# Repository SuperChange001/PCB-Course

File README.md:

# PCB Course

Materials for the PCB course

## Preparation
1. Please clone this repo to to your PC
2. Download and install Eagele with the version which matches your Operating System:
   - [Download Eagle](https://www.autodesk.com/products/eagle/free-download)
   - The first time you open the Eagle, it may ask you to log in, there you should use your university email address to register and log in.

## Folder structure

``` text
.
├── xmas tree
│   ├── tree_pcb.brd
│   ├── tree_pcb.sch
│   └── xmas_tree.lbr
├── esp32 shield
│   ├── design_template
│   ├── old_design
│   └── esp32_shield.lbr
├── utils
│   ├── jlcpcb_cam.cam
│   ├── jlc_pcb.dru
│   ├── voltera-cam.cam
│   └── voltera-dru.dru
└── README.md
```
1. `xmas tree` contains the material for the beginner course
2. `esp32 shield` contains the material for the advanced course
3. `utils` host files that are shared

## Acknowledgement
The christmas tree project is inspird by
* [Brian-Lough-Hardware](https://github.com/witnessmenow/Brian-Lough-Hardware/tree/main/Hardware/Side%20Mounted%20LED%20Tester)

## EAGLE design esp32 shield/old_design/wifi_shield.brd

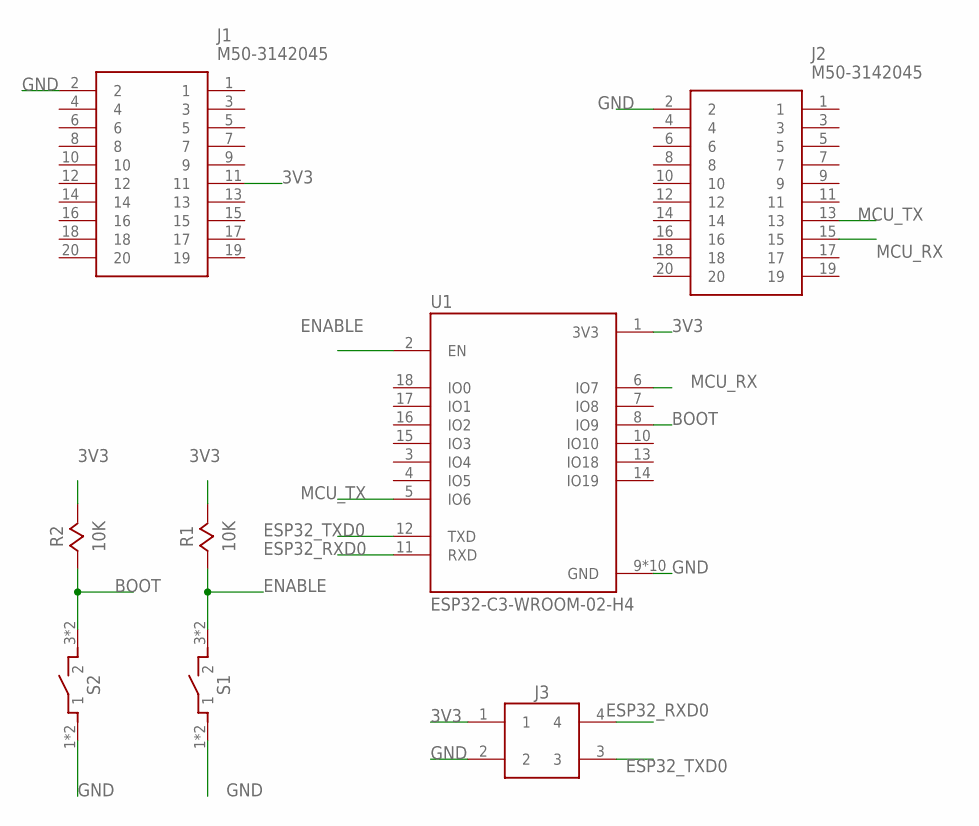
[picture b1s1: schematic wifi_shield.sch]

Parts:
J1, J2: M50-3142045; M503142045
J3: MALE_HEADER_4X1; 4X1_HEADER
R1, R2: 10K; 0805
S1, S2: TACTILE-SWITCH
U1: ESP32-C3-WROOM-02-H4; MODULE_ESP32-C3-WROOM-02-H4

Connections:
3V3: J1.11, J3.1, R1.2, R2.2, U1.1 (3V3)
BOOT: R2.1, S2.3 (2), S2.4 (2), U1.8 (IO9)
ENABLE: R1.1, S1.3 (2), S1.4 (2), U1.2 (EN)
ESP32_RXD0: J3.4, U1.11 (RXD)
ESP32_TXD0: J3.3, U1.12 (TXD)
GND: J1.2, J2.2, J3.2, S1.1, S1.2 (1), S2.1, S2.2 (1), U1.9 (GND), U1.19 (GND), U1.20 (GND), U1.21 (GND), U1.22 (GND), U1.23 (GND), U1.24 (GND), U1.25 (GND), U1.26 (GND), U1.27 (GND)
MCU_RX: J2.15, U1.6 (IO7)
MCU_TX: J2.13, U1.5 (IO6)

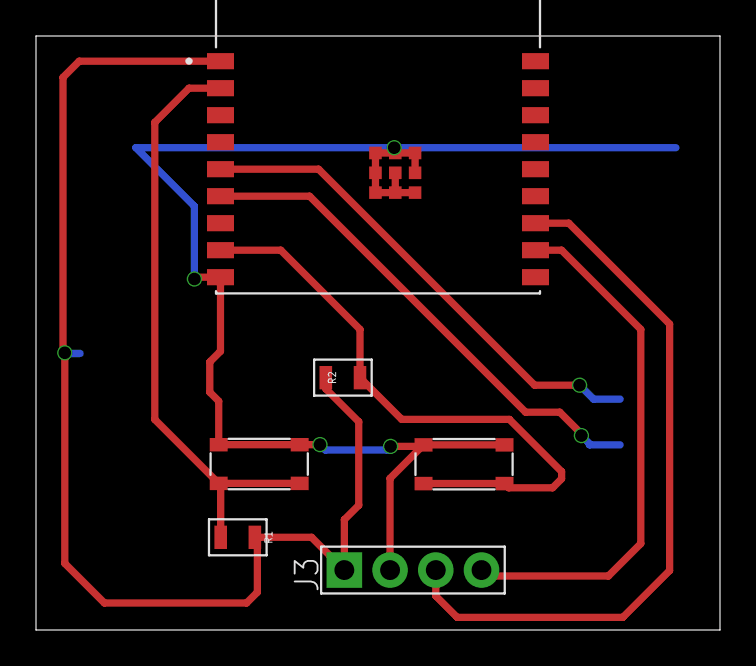
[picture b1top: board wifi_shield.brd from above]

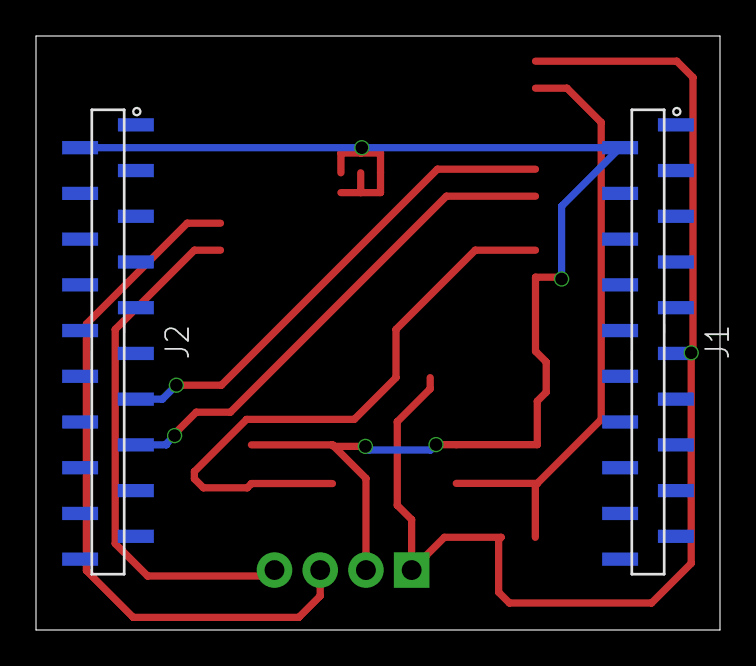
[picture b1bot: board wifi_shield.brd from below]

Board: 2 copper layers, 38.0 x 33.0 mm, 8 parts (2 on the bottom side), 8 nets.

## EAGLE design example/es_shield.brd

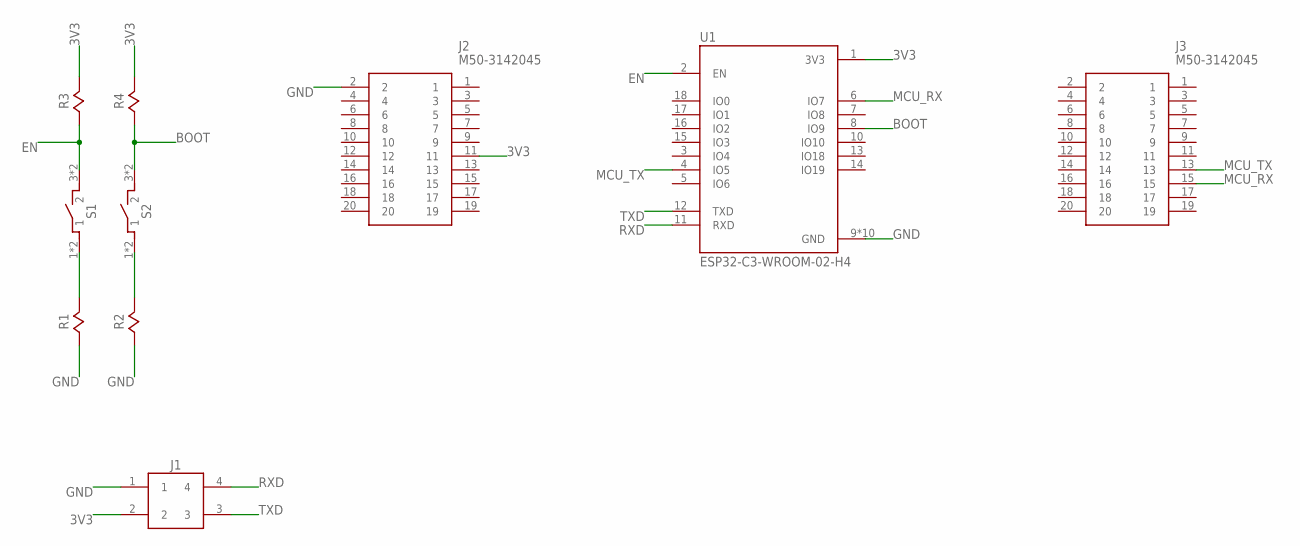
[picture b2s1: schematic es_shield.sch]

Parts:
J1: MALE_HEADER_4X1; 4X1_HEADER
J2, J3: M50-3142045; M503142045
R1, R2, R3, R4: RESISTOR; 0805
S1, S2: TACTILE-SWITCH
U1: ESP32-C3-WROOM-02-H4; MODULE_ESP32-C3-WROOM-02-H4

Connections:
3V3: J1.2, J2.11, R3.2, R4.2, U1.1 (3V3)
BOOT: R4.1, S2.3 (2), S2.4 (2), U1.8 (IO9)
EN: R3.1, S1.3 (2), S1.4 (2), U1.2 (EN)
GND: J1.1, J2.2, R1.1, R2.1, U1.9 (GND), U1.19 (GND), U1.20 (GND), U1.21 (GND), U1.22 (GND), U1.23 (GND), U1.24 (GND), U1.25 (GND), U1.26 (GND), U1.27 (GND)
MCU_RX: J3.15, U1.6 (IO7)
MCU_TX: J3.13, U1.4 (IO5)
unnamed: R1.2, S1.1, S1.2 (1)
unnamed: R2.2, S2.1, S2.2 (1)
RXD: J1.4, U1.11 (RXD)
TXD: J1.3, U1.12 (TXD)

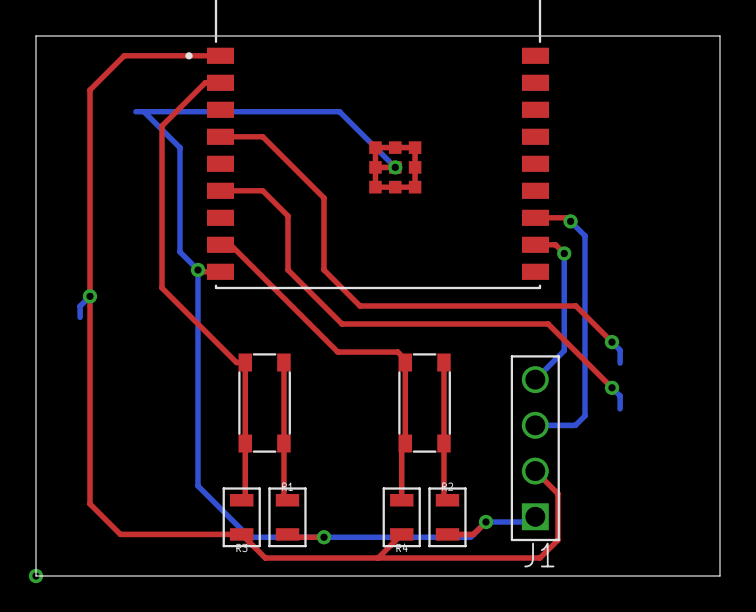
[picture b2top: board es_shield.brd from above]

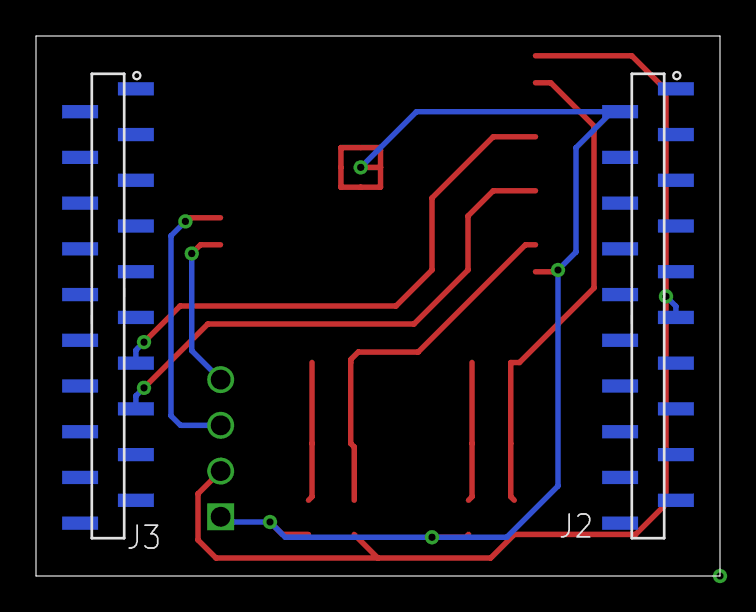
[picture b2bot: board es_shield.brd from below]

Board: 2 copper layers, 38.0 x 30.0 mm, 10 parts (2 on the bottom side), 10 nets.

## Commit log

2022-04-28 first update before the course
2022-11-16 backup
2022-11-17 back up
2022-11-17 basic course done
2022-11-17 remove files
2022-11-17 finished both sessions
2022-11-17 modify readme
